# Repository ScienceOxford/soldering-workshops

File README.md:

# soldering-workshops
PCB designs for soldering workshops, containing basic components - KiCAD files &amp; gerbers

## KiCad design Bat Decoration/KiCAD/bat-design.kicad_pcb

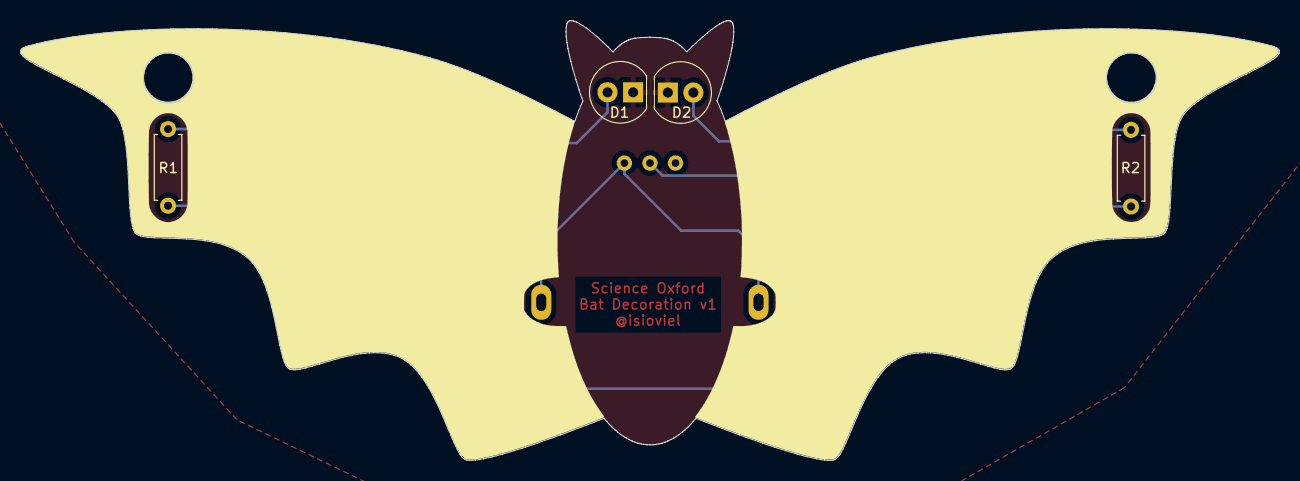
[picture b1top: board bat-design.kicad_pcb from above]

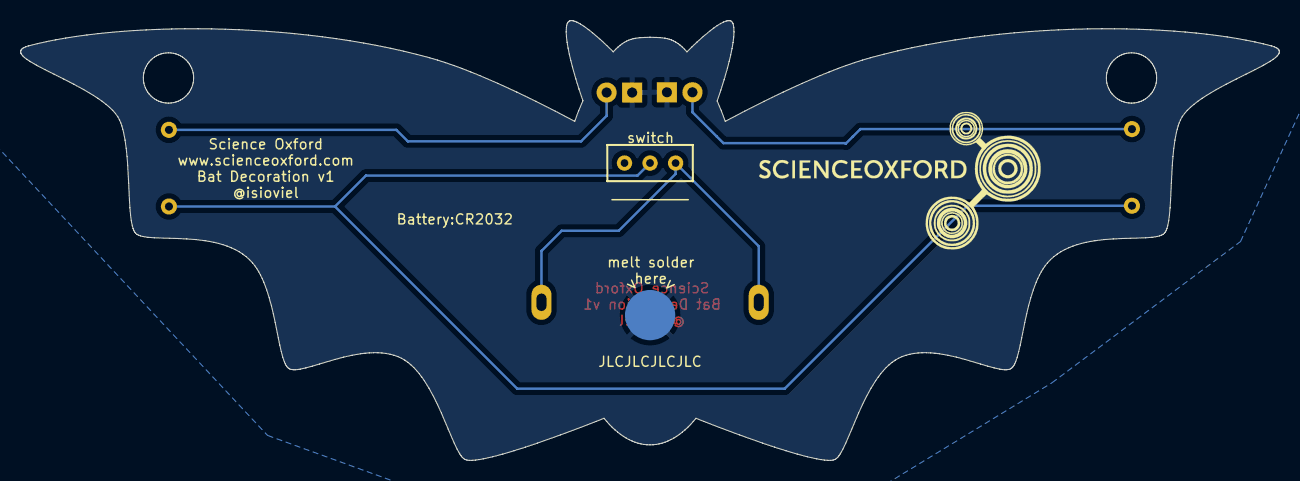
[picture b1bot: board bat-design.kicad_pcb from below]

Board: 2 copper layers, 125.1 x 43.7 mm, 7 parts (2 on the bottom side), 5 nets.

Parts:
Battery:CR2032: battery_holder; battery_holder2
D1, D2: LED; LED_5mm_Radial-flipped
R1, R2: R; R_Axial_DIN0207_L6.3mm_D2.5mm_P7.62mm_Horizontal
Ref**: Val**; bat-screen
switch: EG1218; slide_switch

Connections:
GND: Battery:CR2032.3, D1.1, D2.1
unnamed: Battery:CR2032.1, Battery:CR2032.2, switch.1
unnamed: D1.2, R1.2
unnamed: D2.2, R2.2
unnamed: R1.1, R2.1, switch.2

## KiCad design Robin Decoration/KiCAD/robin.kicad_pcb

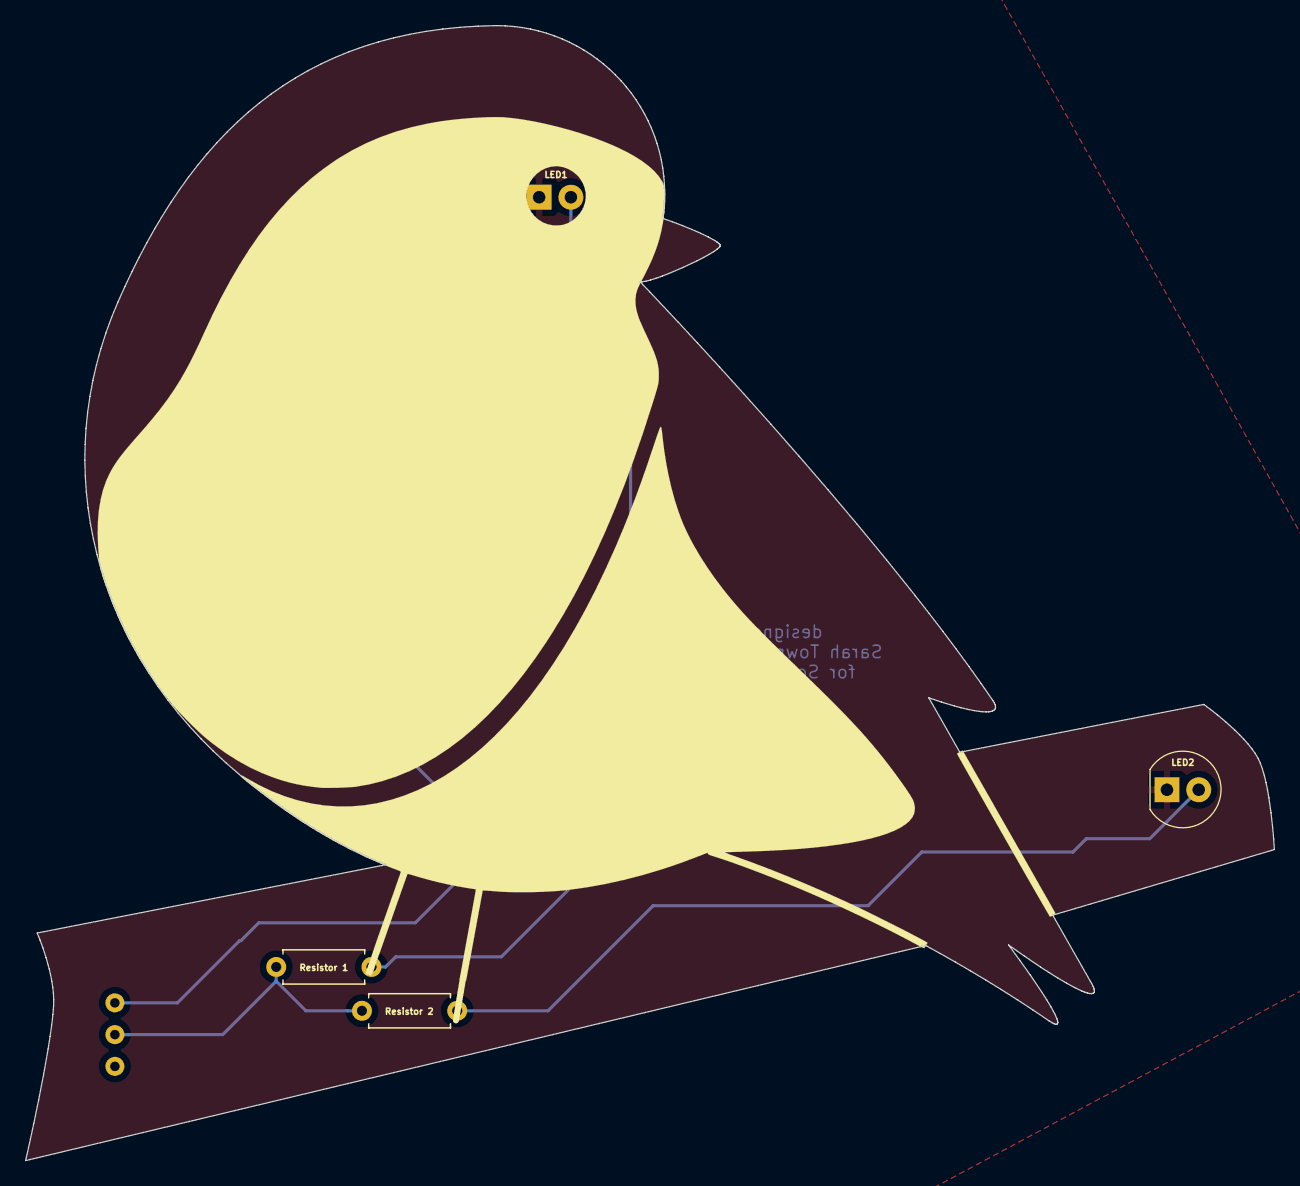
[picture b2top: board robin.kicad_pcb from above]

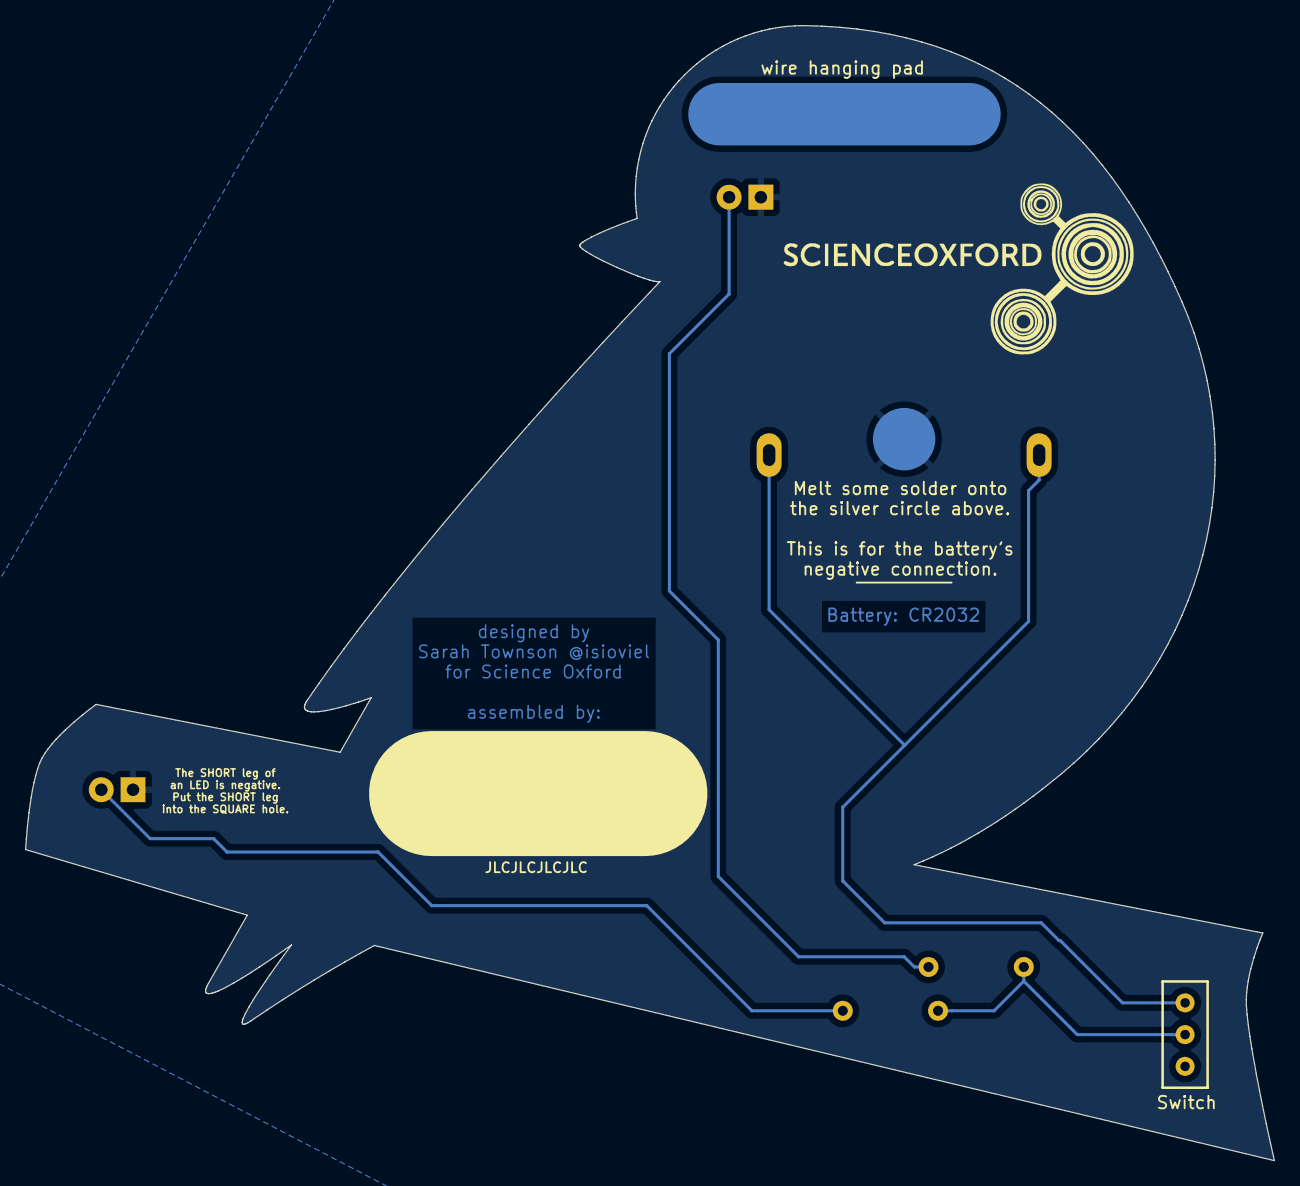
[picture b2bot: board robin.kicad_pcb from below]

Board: 2 copper layers, 99.9 x 90.8 mm, 7 parts (3 on the bottom side), 5 nets.

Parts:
BAT1: battery_holder; battery_holder2
LED1, LED2: LED; LED_5mm_Radial--flipped
Resistor 1, Resistor 2: R; R_Axial_DIN0207_L6.3mm_D2.5mm_P7.62mm_Horizontal
Switch: EG1218; slide_switch
wire hanging pad: hanger-pad

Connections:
GND: BAT1.3, LED1.1, LED2.1
unnamed: BAT1.1, BAT1.2, Switch.1
unnamed: LED1.2, Resistor 1.2
unnamed: LED2.2, Resistor 2.2
unnamed: Resistor 1.1, Resistor 2.1, Switch.2

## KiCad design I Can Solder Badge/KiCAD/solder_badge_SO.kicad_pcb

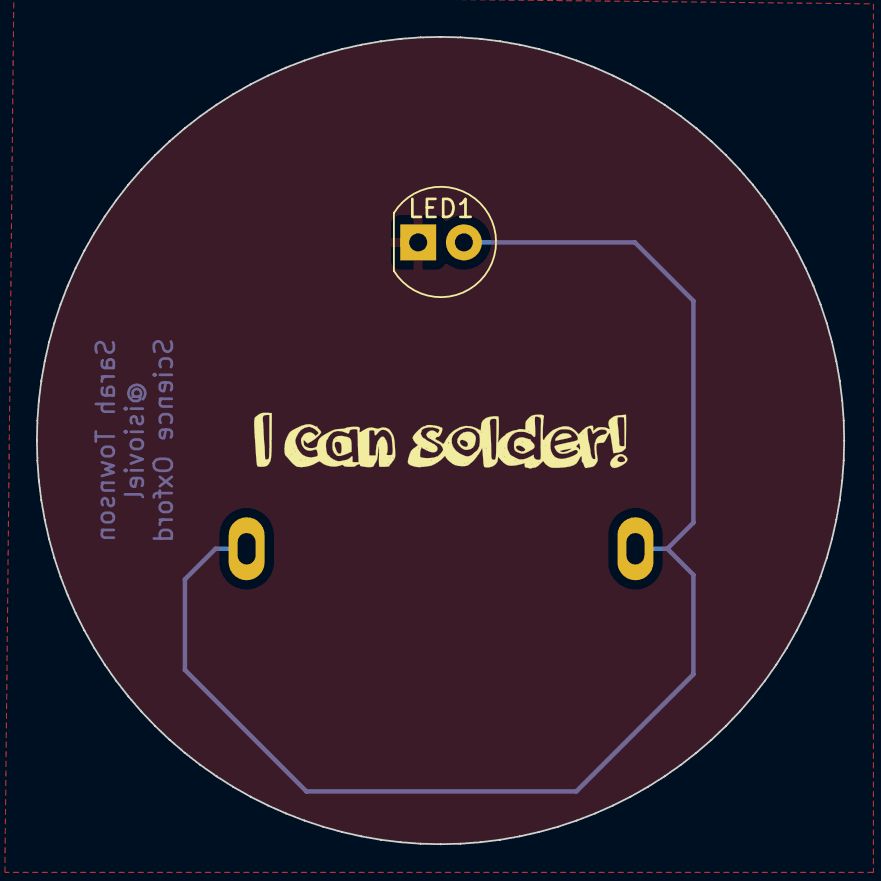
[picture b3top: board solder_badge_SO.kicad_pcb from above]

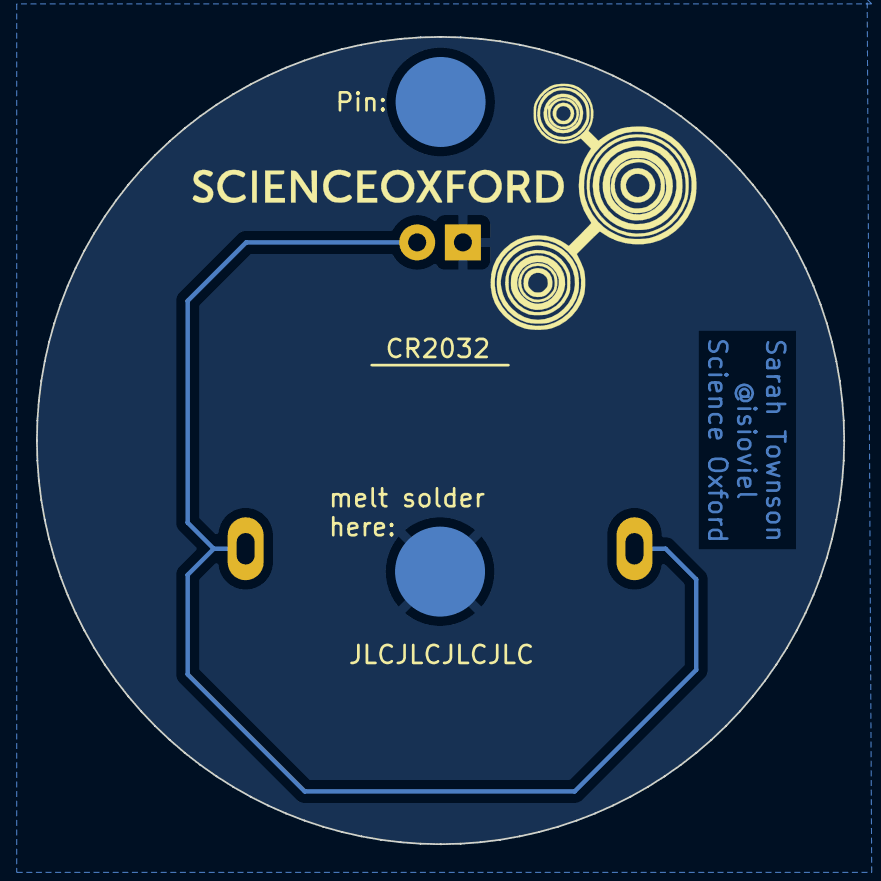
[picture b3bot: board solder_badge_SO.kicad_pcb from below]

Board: 2 copper layers, 44.9 x 44.8 mm, 3 parts (2 on the bottom side), 2 nets.

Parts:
CR2032: battery_holder; cr2032_holder
LED1: LED; LED_5mm
Pin:: pad

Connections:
GND: CR2032.3, LED1.1
unnamed: CR2032.1, CR2032.2, LED1.2

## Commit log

2025-02-18 Create LICENSE
2025-02-18 Add: I Can Solder Badge v2
    KiCad files + Gerbers for the 'I Can Solder' badge
2025-02-18 Updated files
2025-02-18 Add: Robin Decoration
    KiCAD files + Gerbers for the Robin Decoration
2025-02-18 Add .svg
    Robin SVG file for edge cut & silkscreen
2025-02-18 Add: Bat Decoration
    KiCAD files & gerbers
